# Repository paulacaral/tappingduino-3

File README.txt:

Los archivos "circuito vx" son las distintas versiones del archivo de eagle con el circuito del tappingduino. Cada versión se acerca un poco más a la versión final.
A partir de ahora, la versión 4 que es la última subida, será la que se vaya modificando y haciéndole commits.

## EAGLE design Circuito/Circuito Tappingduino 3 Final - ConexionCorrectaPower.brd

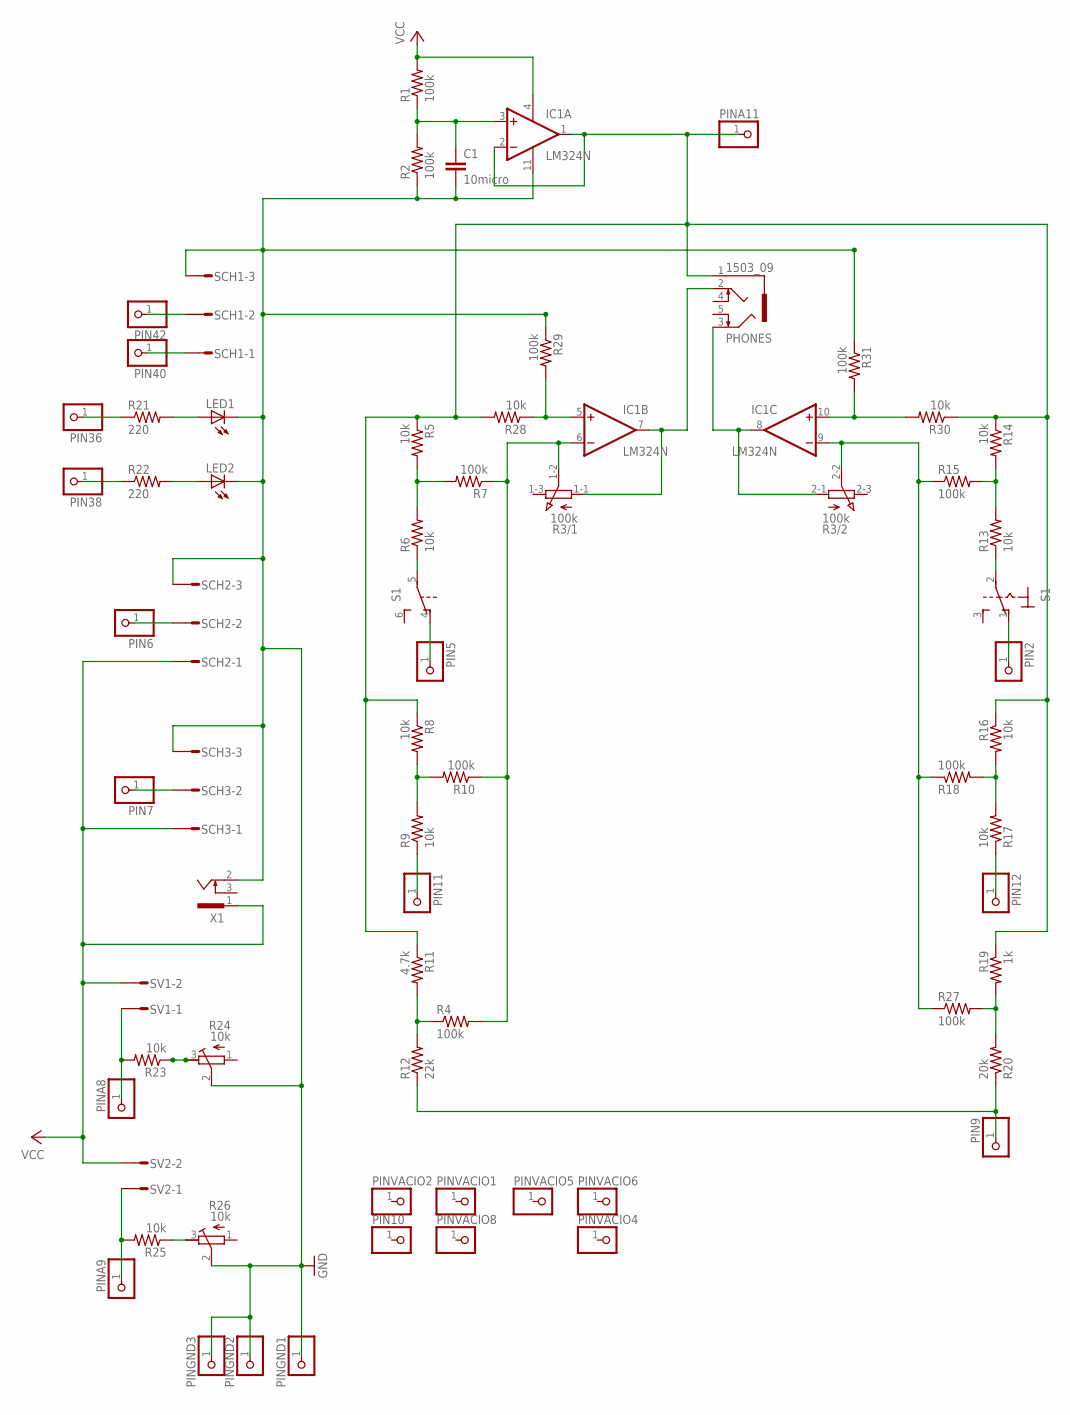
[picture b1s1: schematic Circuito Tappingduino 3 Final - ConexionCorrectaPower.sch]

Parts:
C1: 10micro; C025-030X050
IC1: LM324N; DIL14
LED1, LED2: LED_ELD260; LED_LD260
PHONES: 1503_09
PIN2, PIN5, PIN6, PIN7, PIN9, PIN10, PIN11, PIN12, PIN36, PIN38, PIN40, PIN42: PINHD-1X1; 1X01
PINA8, PINA9, PINA11: PINHD-1X1; 1X01
PINGND1, PINGND2, PINGND3: PINHD-1X1; 1X01
PINVACIO1, PINVACIO2, PINVACIO4, PINVACIO5, PINVACIO6, PINVACIO8: PINHD-1X1; 1X01
R1, R2, R4, R7, R10, R15, R18, R27, R29, R31: 100k; 0207/7
R3: 100k; 3RP/1610G
R5, R6, R8, R9, R13, R14, R16, R17, R23, R25, R28, R30: 10k; 0207/7
R11: 4.7k; 0207/7
R12: 22k; 0207/7
R19: 1k; 0207/7
R20: 20k; 0207/7
R21, R22: 220; 0207/7
R24, R26: 10k; RTRIM64W
S1: 320-938
SCH1, SCH2, SCH3: L03P
SV1, SV2: L02P
X1: SCD-014A; SCD-014-A

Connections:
GND: C1.2, IC1.11 (V-), LED1.K (C), LED2.K (C), PINGND1.1, PINGND2.1, PINGND3.1, R2.1, R24.2 (S), R26.2 (S), R29.1, R31.1, SCH1.3, SCH2.3, SCH3.3, X1.2
unnamed: C1.1, IC1.3 (+IN), R1.1, R2.2
unnamed: R25.1, R26.3 (E)
unnamed: PIN11.1, R9.1
unnamed: IC1.6 (-IN), R3.1-2 (S), R4.2, R7.1, R10.1
unnamed: R5.2, R6.2, R7.2
unnamed: R6.1, S1.5
unnamed: PIN5.1, S1.4 (O)
unnamed: IC1.1 (OUT), IC1.2 (-IN), PHONES.1, PINA11.1, R5.1, R8.1, R11.1, R14.1, R16.1, R19.1, R28.2, R30.1
unnamed: R8.2, R9.2, R10.2
unnamed: IC1.10 (+IN), R30.2, R31.2
unnamed: R4.1, R11.2, R12.2
unnamed: IC1.9 (-IN), R3.2-2 (S), R15.1, R18.1, R27.1
unnamed: R13.2, R14.2, R15.2
unnamed: R13.1, S1.2
unnamed: PIN2.1, S1.1 (O)
unnamed: IC1.5 (+IN), R28.1, R29.2
unnamed: R19.2, R20.2, R27.2
unnamed: R16.2, R17.2, R18.2
unnamed: PIN12.1, R17.1
unnamed: PIN9.1, R12.1, R20.1
unnamed: PIN42.1, SCH1.2
unnamed: PIN40.1, SCH1.1
unnamed: LED1.A, R21.2
unnamed: PIN36.1, R21.1
unnamed: LED2.A, R22.2
unnamed: PIN38.1, R22.1
unnamed: PIN7.1, SCH3.2
unnamed: PIN6.1, SCH2.2
unnamed: IC1.8 (OUT), PHONES.3, R3.2-1 (A)
unnamed: PINA8.1, R23.2, SV1.1
unnamed: R23.1, R24.3 (E)
unnamed: PINA9.1, R25.2, SV2.1
unnamed: IC1.7 (OUT), PHONES.2, R3.1-1 (A)
VCC: IC1.4 (V+), R1.2, SCH2.1, SCH3.1, SV1.2, SV2.2, X1.1

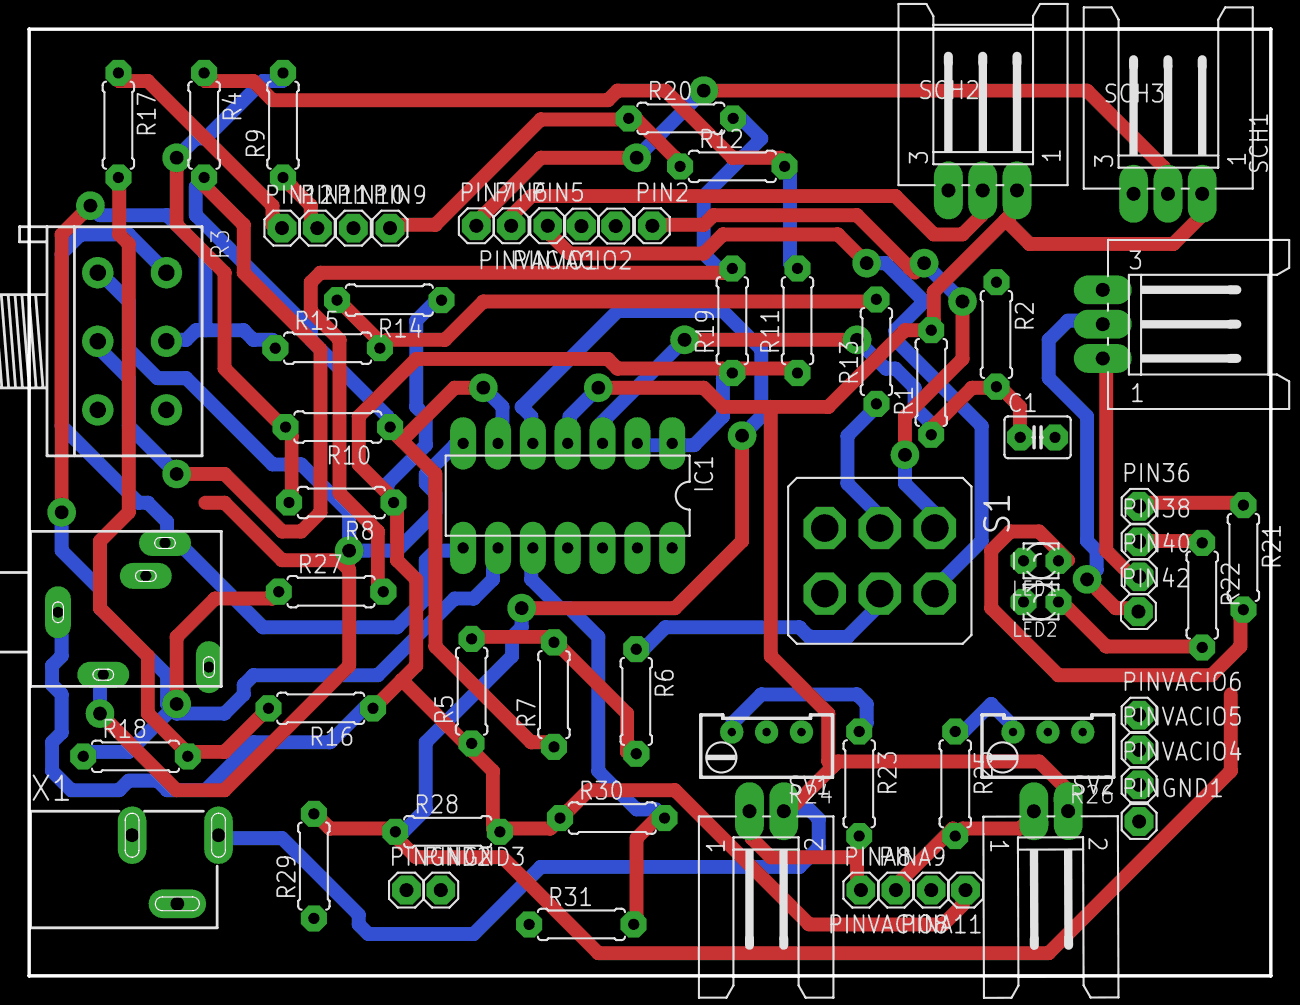
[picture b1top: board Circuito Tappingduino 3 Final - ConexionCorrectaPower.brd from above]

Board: 2 copper layers, 90.5 x 69.0 mm, 67 parts (0 on the bottom side), 35 nets.

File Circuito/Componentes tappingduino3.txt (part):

Partlist exported from /home/paula/Descargas/tappingduino-3-master/circuito v6-pv.sch at 27/8/19 16:07

Part      Value   Device          Package      Description                                    MF MPN OC_FARNELL OC_NEWARK SPICEMODEL SPICEPREFIX SPICEPREFIXL SPICETYPE
C1        10micro C-EU025-030X050 C025-030X050 CAPACITOR, European symbol                                                            C                                 
IC1       LM324N  LM324N          DIL14        OP AMP                                                                                X                                 
LED1              LED_ELD260      LED_LD260    LED                                                                        DMOD       D                        diode    
LED2              LED_ELD260      LED_LD260    LED                                                                        DMOD       D                        diode    
PHONES    1503_09 1503_09         1503_09      Jack connectors according to JISC 6560, 3.5 mm        1243244    unknown              X                                 
PIN2              PINHD-1X1       1X01         PIN HEADER                                                                            X                                 
PIN5              PINHD-1X1       1X01         PIN HEADER                                                                            X                                 
PIN6              PINHD-1X1       1X01         PIN HEADER                                                                            X                                 
PIN7              PINHD-1X1       1X01         PIN HEADER                                                                            X                                 
PIN9              PINHD-1X1       1X01         PIN HEADER                                                                            X                                 
PIN10             PINHD-1X1       1X01         PIN HEADER                                                                            X                                 
PIN11             PINHD-1X1       1X01         PIN HEADER                                                                            X                                 
PIN12             PINHD-1X1       1X01         PIN HEADER                                                                            X                                 
PIN36             PINHD-1X1       1X01         PIN HEADER                                                                            X                                 
PIN38             PINHD-1X1       1X01         PIN HEADER                                                                            X                                 
PIN40             PINHD-1X1       1X01         PIN HEADER                                                                            X                                 
PIN42             PINHD-1X1       1X01         PIN HEADER                                                                            X                                 
PINA8             PINHD-1X1       1X01         PIN HEADER                                                                            X                                 
PINA9             PINHD-1X1       1X01         PIN HEADER                                                                            X                                 
PINGND1           PINHD-1X1       1X01         PIN HEADER                                                                            X                                 
PINGND2           PINHD-1X1       1X01         PIN HEADER                                                                            X                                 
PINGND3           PINHD-1X1       1X01         PIN HEADER                                                                            X                                 
PINVACIO1         PINHD-1X1       1X01         PIN HEADER                                                                            X                                 
PINVACIO2         PINHD-1X1       1X01         PIN HEADER                                                                            X                                 
PINVACIO4         PINHD-1X1       1X01         PIN HEADER                                                                            X                                 
PINVACIO5         PINHD-1X1       1X01         PIN HEADER                                                                            X                                 
PINVACIO6         PINHD-1X1       1X01         PIN HEADER                                                                            X                                 
PINVACIO7         PINHD-1X1       1X01         PIN HEADER                                                                            X                                 
PINVACIO8         PINHD-1X1       1X01         PIN HEADER                                                                            X                                 
R1        100k    R-US_0207/7     0207/7       RESISTOR, American symbol                                                             R                                 
R2        100k    R-US_0207/7     0207/7       RESISTOR, American symbol                                                             R                                 
R3        100k    3RP/1610G       3RP/1610G    16mm Potentiometer two level                                                          J                                 
R4        100k    3RP/1610G       3RP/1610G    16mm Potentiometer two level                                                          J                                 
R5        10k     R-US_0207/7     0207/7       RESISTOR, American symbol                                                             R                                 
R6        10k     R-US_0207/7     0207/7       RESISTOR, American symbol                                                             R                                 
R7        100k    R-US_0207/7     0207/7       RESISTOR, American symbol                                                             R                                 
R8        10k     R-US_0207/7     0207/7       RESISTOR, American symbol                                                             R                                 
R9        10k     R-US_0207/7     0207/7       RESISTOR, American symbol                                                             R                                 
R10       100k    R-US_0207/7     0207/7       RESISTOR, American symbol                                                             R                                 
R11       10k     R-US_0207/7     0207/7       RESISTOR, American symbol                                                             R                                 
R12       10k     R-US_0207/7     0207/7       RESISTOR, American symbol                                                             R                                 
R13       10k     R-US_0207/7     0207/7       RESISTOR, American symbol                                                             R                                 
R14       10k     R-US_0207/7     0207/7       RESISTOR, American symbol                                                             R                                 
R15       100k    R-US_0207/7     0207/7       RESISTOR, American symbol                                                             R                                 
R16       10k     R-US_0207/7     0207/7       RESISTOR, American symbol                                                             R                                 
R17       10k     R-US_0207/7     0207/7       RESISTOR, American symbol                                                             R                                 
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
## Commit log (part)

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2019-08-16 Circuito v4 con poligonos top layer
    Se agregaron poligonos en layer 41 tRestrict, alrededor de los pads de algunos elementos.
2019-08-20 poligonos layer tRestrict agrandados
2019-08-20 Agregado de recuadros con texto
    Muestran que es cada parte delcircuito
2019-08-20 Agregado de recuadros con texto a sch
    Clasifican cada parte del circuito
2019-08-20 Layout tal que el routeado da 9 vias
2019-08-20 Layout 100% y 10 vias
    Hay que restringirle la posibilidad de vias debajo de los componentes
2019-08-22 Correccion de algunos poligonos vRestrict
    Se corrigen poligonos para que las vias no queden pegadas a los elementos. No se guarda la version con pistas, pero es posible mover las vias que quedan muy pegadas. Esta version es la previa a incor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
2019-08-22 board y sch con elemento ICSP del arduino incluido
2019-08-22 Agrego vRestrict en OpAmp y Switchs
2019-08-22 última v6 del día
    Creo que no tiene modificaciones salvo que intenté hacer el mapeo para la simulación. Todo lo demás debería estar igual. Se guarda por las dudas.
2019-08-26 Circuito arduino viejo
2019-08-26 Chequeo de lado izq y der de phones
    Chequeo de lado izq y der de phones. Cambio nombre de los pines de cada parte en base a eso.
    Uso:
    Estimulo Izq PIN 11
    Estimulo Der PIN 12
    Feedback Izq PIN 2
    Feedback Der PIN 5
2019-08-26 Cambio 2 switchs simples por 1 doble
    Los switches simples que se van son los que controlan el feedback
2019-08-26 Cambio 2 switch dobles por 1 simple
    Las conexiones del nuevo switch quedaron bien hechas.
    El switch doble es Toggle switch 320-938
2019-08-26 De ahora en mas se modifica el archivo circuito v6-pv
    Esta version tiene los nombres correctos de los pines + estan acomodados en sus lugares + un switch doble en vez de dos simples + se borro el pin vacio en la posicion 13 que quedaba en la punta y ya 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
    Tiene un autoroute de 100% con 14 vias.
2019-08-26 Prints de layers de cobre
    Solo consideramos los planos, pads y vias.
    Seleccionando view y las capas que corresponden.
2019-08-27 Tabla de componentes exportada de eagle
    La tabla con lo que hace falta comprar/hay esta en un excell en drive
2019-08-29 Lista de elementos + parametros
2019-09-05 Archivo de arduino que no deja ruido
    SOL1 = diciendole a los pines que en TickOff lean una matriz que es un voltaje constante a 2.3V (tierra virtual)
    SOL2 = poniendo los tres bloques (feedback, estimulo y ruido blanco) a tierra normal envez de tierra virtual.
    Esta segunda solucion no esta probada. fuearmado el circuito pero algo raro pasa en la conexion de los auriculares.
2019-09-09 Nuevas versiones de codigo
    pruebas 2: es una nueva version de UnTimer...-SOL1 en la que cambiamos la resolucion de un numero medio random a 65536 y ademas testeamos ruido y feedback. Ruido mete ruido, pero estamos tratanto al 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
    prueba_librerias_Ulises no lo tocamos, lo subo para tenerlo
    SineTones_unq.cpp y .h fueron sacadas de la carpeta de Ulises. Son las librerias y ahi se trata al timer2 como corresponde
    pruebas3 es prueba_librerias_Ulises. Salvo activar y desactivar cosas, es igual. lo que si cambiamos es la libreria SineTones_unq.cpp que lee, donde cambiamos los pines de left a right. FALTA UNIFICA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
2019-09-12 ACTUALIZACION CIRCUITO
    Cambios
    1- Chequeo de pines/canales/izq y der:
    IZQ - B - 12,9 Y 2
    DER - A - 11,10Y5
    2- CONEXION TIERRA VIRTUAL A PIN A11
    3- CAMBIO DE RESISTENCIAS PARA EL PIN DEL RUIDO
2019-09-17 ultimo circuito con routeo 100% y 15 vias
2019-09-23 Actualizacion de resistencias para ruido
    Resistencias 200k, 100k y 10k dejan un volumen de ruido tal que no es muy molesto con el estimulo
    pero lo suficientemente molesto porque es lo que da el valor maximo
    el chiste seria manejar el ruido desde el soft despues
2019-09-26 enlimpio.ino
    enlimpio-stimfdbk.ino esel pasaje en limpio del codigo de leo (UnTimerControla..) que solo tiene stim y feedback y anda
    enlimpio.ino es el mismo archivo pero con el agregado de ruido
2019-09-26 Ultima version de circuito + codigo que anda
    Cambiamos la configuracion de los registros de los timers 1 y 3 para darle mas tiempo al ISR para hacer las tareas.
    Lo mismo pero con la configuracion correspondiente al timer 2.
    CONFIGURACION DE LOS TIMERS
    TIMER 1 y 3
    >Sin prescaling
    >Fast PWM 9-bit TOP = 0x010FF = 512 // Esto hace que en la rampa de overflow vaya hasta 512 en vez de hasta 255, dandole mas tiempo al ISR antes de cambiar de lectura en la tabla del seno
2019-10-01 Enlimpio en carpeta
    Para poder abrirlo desde arduino necesito que el .ino este dentro de una carpeta que se llame igualque el archivo, asi que se genero esto automaticamente
2019-10-01 Separo versiones de enlimpio
    Agrego enlimpio version con lectura de tierra virtual y para que arduino pueda abrirlo, tiene su propia carpeta
2019-10-03 enlimpio-TickOnWhile
    enlimpio-LecturaVG solo tiene cambios de prueba, comentar y descomentar los else en los ISR, etc.
    enlimpio-TickOnWhile es una nueva version de LecturaVG en la que tiene el tickOnWhile para leer en el loop, en vez de estar leyendo los ifs ahi, pero ademas ya esta pasado en limpio que se borró todo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
    Agrego ademas que el timer2 lea tierra virtualcuando esté apagado. Le doy inputs a generatenoise para poder setearle el volumen (amplitud respecto a tv) desde el tickon, etc.
2019-10-03 Creacion enlimpio-Optimizacion
    enlimpio-Optimizacion es la siguiente version a enlimpio-TickOnWhile
    Cambios hechos:
    - Se cambian los if en TickOn, TickOff y TickOnWhile por switchs
    - Se saca la definicion de int pin = pinVG usando directamente pinVG
    - Se reemplaza osc3A/B por directamente la escritura en OCR3A/B (same para timer1). Esto hace que la lectura de la tabla se haga en esa misma "corrida" y no en la siguiente como pasaba antes.
    -Renombrar TickOn y TickOff como PlaySound y StopSound. (TickOnWhile = PlaySoundWhile)
2019-10-15 Controlador e interduino.m
    Controlador esla version de enlimpio-Optimizacion que tiene incorporada la parte de leer los parametros de una rutina en matlab, ademas de guadar las variables y etc. COMPILA.
    interaduino_pruebas.m deberia mandarle los parametros a Controlador y recibir los resultados. NO estoy pudiendo comunicarme conel arduino
2019-10-21 Circuito versiones para imprimir
2019-10-21 Organizacion en carpetas
2019-10-21 Actualizacion Circuito correcto
    Circuito correcto y board exportado a tamaño RECONTRACHEQUEADO
2019-10-21 Actualizacion board y copias correcto
    tamaño, blanco y negro y espejamiento correcto
2019-10-22 Version de Controlador sin if de apagado en el loop
    Se hace el cambio para que el apagado del sonido no este en el loop, sino que suceda en el timer
2019-10-22 Actualizacion ControladorSoundWhile
    Cambiamos la forma en que corta el sonido en el timer.
    Le agregue el apagado de s, f y n en el cierre del trial, por las dudas.
    Esta chequeado que el sonido anda con SoundSwitch
    Agregue al circuito el sensor de fuerza para ver si el feedback suenacuando tiene que sonar solamente y anda tambien.
2019-10-24 Actualizacion controlador
    Se agrega asincronia correctamente en python
    Se agrega que el uso de left y right (tanto de S como de F) sea un parametro que se le da a arduino desde python
2019-10-28 Agregado de flags izq y der
    Se le agrega una diferenciaci'on entre los flags right y left y ademas se ponen dentro del soundSwitch. Esto porque corria mas veces en el timer que en el loop entonces, el audio que leia segundo en 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
    Asi funciona.
    Tambien se tuvoque agregar una condicion en el if del loop que fuese
    if ( pas'o el tiempo necesario Y (flag_der=false O flag_izq=false) )
    para que ande con los dos.
    Con esto funciona correctamente recibiendo las ordenes desde python SR, SL, SN, SB, FR, FL, FN, FB
2019-10-28 Python corre trials
    Corre la cantidad de trials indicada. guarda solo si el trial es valido. guarda datos crudos, tiempos de stim, tiempo sde fdbk y asincronias
2019-10-29 Guarda datos en npz
    Controlador que guarda datos de cada trial en un npz. Guarda ademas otro archivo npz que tiene la variable trials que dice cuales fueron validos y cuales no.
2019-10-31 Update Controlador python
    >Guarda el raw en .txt tambien.
    >Considera el caso en que no hay ninguna respuesta y lo pone como trial no valido
    >Guarda las condiciones del trial (guardando el mensaje que se le mando a arduino)
    >Recibe left o right para estimulo y feedback como input
2019-10-31 Controlador eleccion random + nuevo al final
    Ahora cuando te equivocas en un trial, te lo hace repetir pero ese trial te lo pone al final
2019-11-04 Controlador python e Ino
    Actualizacion en ambos para que el ruido blando sea un parametro que se manda dsde pythontambien
    Ino ademas tiene modificada la duraciondel beep porque pruebas para que termine de leer la tabla en 0
2019-11-11 La duracion del beep ya no es un input para arduino
2019-11-11 Los beeps terminan suave
    La duracion del beep ahora se hace en funcion de la cantidad de veces que lee la tabla para que el "cierre" sea suave y no se escuche un TACK al final.
    Para eso no solo cambiamos la condicion dela duracion en el timer sino que tambien hicimos una funcion que calcula la cantidad de ciclos que debe hacer para que el tiempo de duracion sea aproximadame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
    es decir, ESTA PENSADO PARA QUE DURE 50ms, si hay que cambiar la duracion hay que modificar esa funcion
2019-11-12 Aleatoreidad de estados
2019-11-15 100% 17 vias - Tamaños correctos
2019-11-19 Versiones definitivas del circuito
    brd, sch, pdfs de bottom, top(mirror) y hoja completa en tamaño carta.
2019-11-28 Tappingduino4 software
2019-12-02 CONEXION POWER CORRECTA
    WARNING: ESTA VERSION DEL ARCHIVO NO TIENE LAS PISTAS FINALES QUE ESTAN IMPRESAS EN LA PLACA. ES UNA SIMPLE CORRECCION A LA CONEXION DEL POWER PARA QUE QUEDE BIEN CONECTADO, PERO LAS PISTAS SON OTRAS.
    Cambio de conexion en las patas del power: antes 2=GND y 3=VCC y ahora 2=GND y 1=VCC
2019-12-06 Cambio nombre sujeto por S00x
    Ahora los archivos se guardan con un pseudonimo dado por S + numero del sujeto.
    Para asegurar que el archivo sea unico, NO CREA un archivo si no existe. Solo lo busca. SI no esta, te pide que lo ubiques en la carpeta correcta (vacio o no) y se fija cual es el numero que le corre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
2019-12-09 Actualizacion controlador
    > Numero de trial en display de pantalla
    > Cambio de F a R en type of event (tambien en arduino)
    > Loop de bloques en for en vez de en while
2019-12-09 Controlador python con exceptions for errors
2019-12-12 Controlador Exceptions
    > Ya no tiene mensajes crueles en la pantalla
    > Las figuras ya no se acumulan, hay solo figura 1 (estimulos, respuestas y señalados los estimulos que tienen par) y figura 2 (asincronias). Con el plt.show() lo muestra a final de cada trial. Sines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
    > El grafico de asincronias tiene unidos los puntitos
    > Dice Responses en el legend del fgrafico en vez de feedback
    > Cuando no hay igual cantidad de stim_paired y resp_paired, se fija de cual hay mas para proporcionar dos errores distintos: te salteaste unestimulo o hay demasiadas respuestas.
2019-12-12 Controlador exceptions y DEMO
    DEMO - es una copia de exceptions en la que solo se ponen 3 condiciones LL, RR y BB, por 10 beeps, dos veces cada condicion, un bloque. Esto es para que pruebe el sujeto. Se guardan los datos en una 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
    Pero funciona igual.
    Controlador Exceptions - le agregue la condicion BB que no la tenia, no se por que
2019-12-16 Actualizacion 1CondxBlock
    HACE CORRECTAMENTE TENER UNA CONDICION POR BLOQUE CON TODO LO DEMAS QUE SE PIDE
    Se sacaron los graficos de la pantalla
    Se agregaron mensajes de error con siglas para que solo lo entendamos nosotros para ir viendo como va el sujeto
    Se agrego una pregunta alfinalde cada bloque para saber que condicion percibio el sujeto para estimulo o respuesta
2019-12-16 ACtualizacion 1condxbloque
    Levanta datos
    +versiondemo
2019-12-18 Probando con pauli
2019-12-19 Actualizacion controlador
    chequea par por par de estimulo y respuesta si la asincronia es menor a 200ms antes de considerarlo un trial valido
    hay una nueva funcion que grafica la asincronia de todos los trials de un bloque de unsujeto
2020-03-11 Reordenamiento de archivos + archivos nuevos
2020-03-18 Corrector de Trials y Testeo de todos los trials
2020-03-18 Analisis de datos y reorganizacion
2020-05-22 código final análisis
